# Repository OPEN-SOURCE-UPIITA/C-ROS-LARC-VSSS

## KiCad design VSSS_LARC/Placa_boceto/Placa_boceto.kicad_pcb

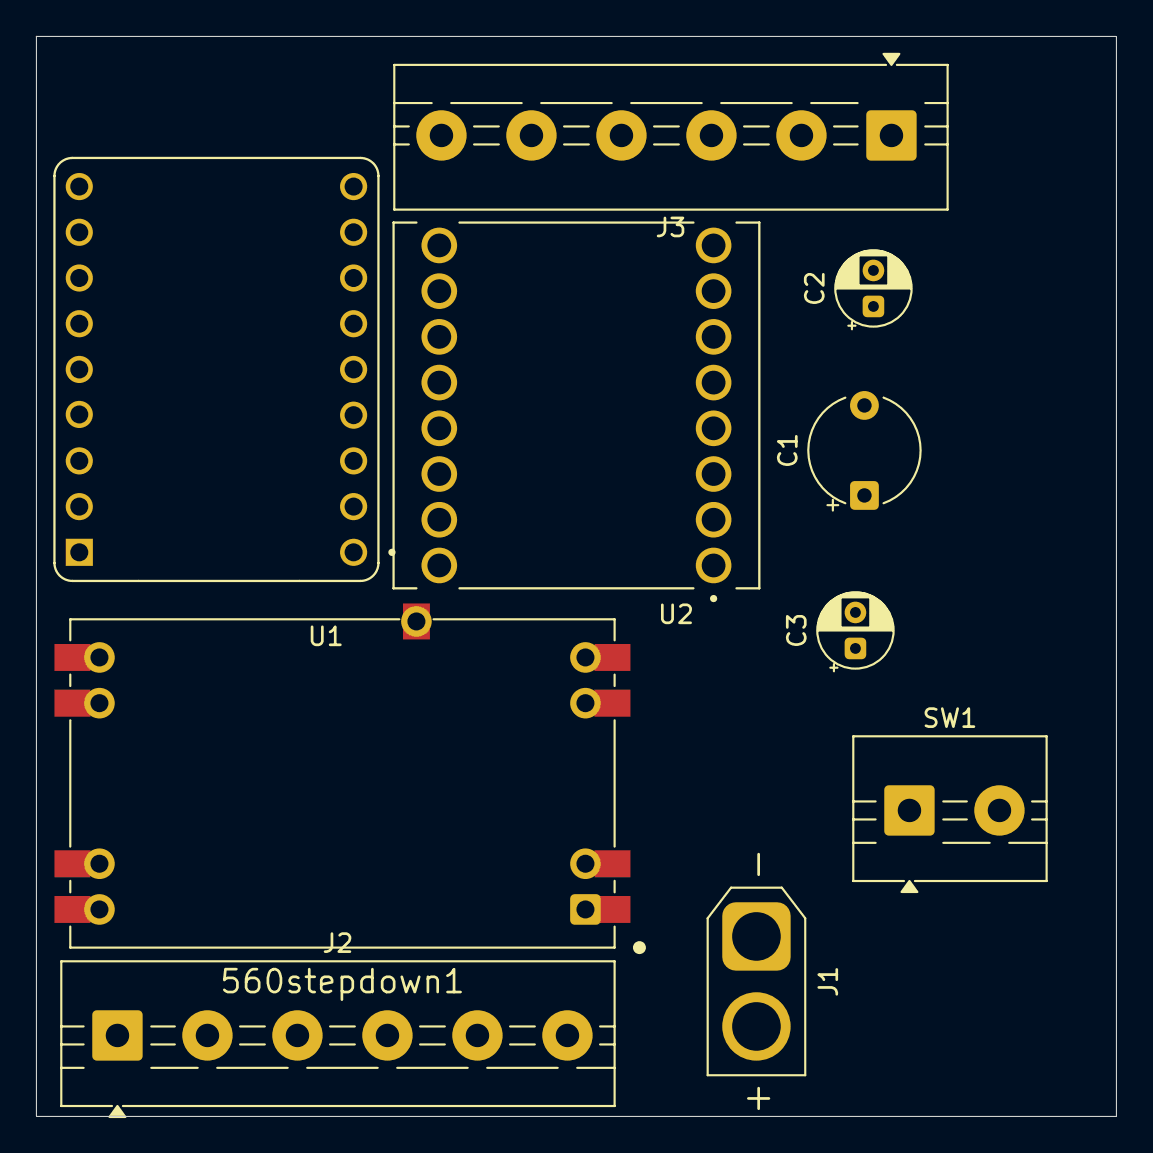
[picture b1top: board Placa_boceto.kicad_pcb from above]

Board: 2 copper layers, 60.0 x 60.0 mm, 10 parts (0 on the bottom side), 16 nets, no tracks yet.

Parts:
560stepdown1: Mini560
C1: C_Polarized; CP_Radial_Tantal_D6.0mm_P5.00mm
C2, C3: C; CP_Radial_D4.0mm_P2.00mm
J1: Conn_01x02_Socket; AMASS_XT30U-M_1x02_P5.0mm_Vertical
J2: Bornera Motor A; TerminalBlock_MaiXu_MX126-5.0-06P_1x06_P5.00mm
J3: Bornera Motor B; TerminalBlock_MaiXu_MX126-5.0-06P_1x06_P5.00mm
SW1: SW_DPST_x2; TerminalBlock_MaiXu_MX126-5.0-02P_1x02_P5.00mm
U1: ESP32-S3-SUPERMINI; ESP32-S3-SuperMini
U2: ROB-14450; MODULE_ROB-14450

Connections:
/5V: 560stepdown1.1 (VOUT(+)), C2.2, C3.2, J2.5, J3.5
/7.2V: 560stepdown1.4 (VIN(-)), C1.1, SW1.1 (A), U2.1 (VM)
/A01: J2.2, U2.4 (A01)
/A02: J2.1, U2.5 (A02)
/B01: J3.2, U2.7 (B01)
/B02: J3.1, U2.6 (B02)
/EN1A: J2.3, U1.3 (PIN_1)
/EN1B: J2.4, U1.4 (PIN_2)
/EN2A: J3.3, U1.6 (PIN_4)
/EN2B: J3.4, U1.7 (PIN_5)
/PWMA: U1.9 (PIN_7), U2.16 (PWMA)
/PWMB: U1.8 (PIN_6), U2.10 (PWMB)
GND: 560stepdown1.2 (VOUT(-)), 560stepdown1.3 (VIN(+)), C1.2, J1.2, J2.6, J3.6, U1.11 (GND), U2.3 (GND), U2.8 (GND), U2.9 (GND)
unnamed: J1.1, SW1.2 (B)
unnamed: C3.1, U1.10 (5V)
unnamed: C2.1, U2.2 (VCC)
